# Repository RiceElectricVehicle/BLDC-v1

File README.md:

# BLDC-v1
REV BLDC Controller Version 1 2019-2020

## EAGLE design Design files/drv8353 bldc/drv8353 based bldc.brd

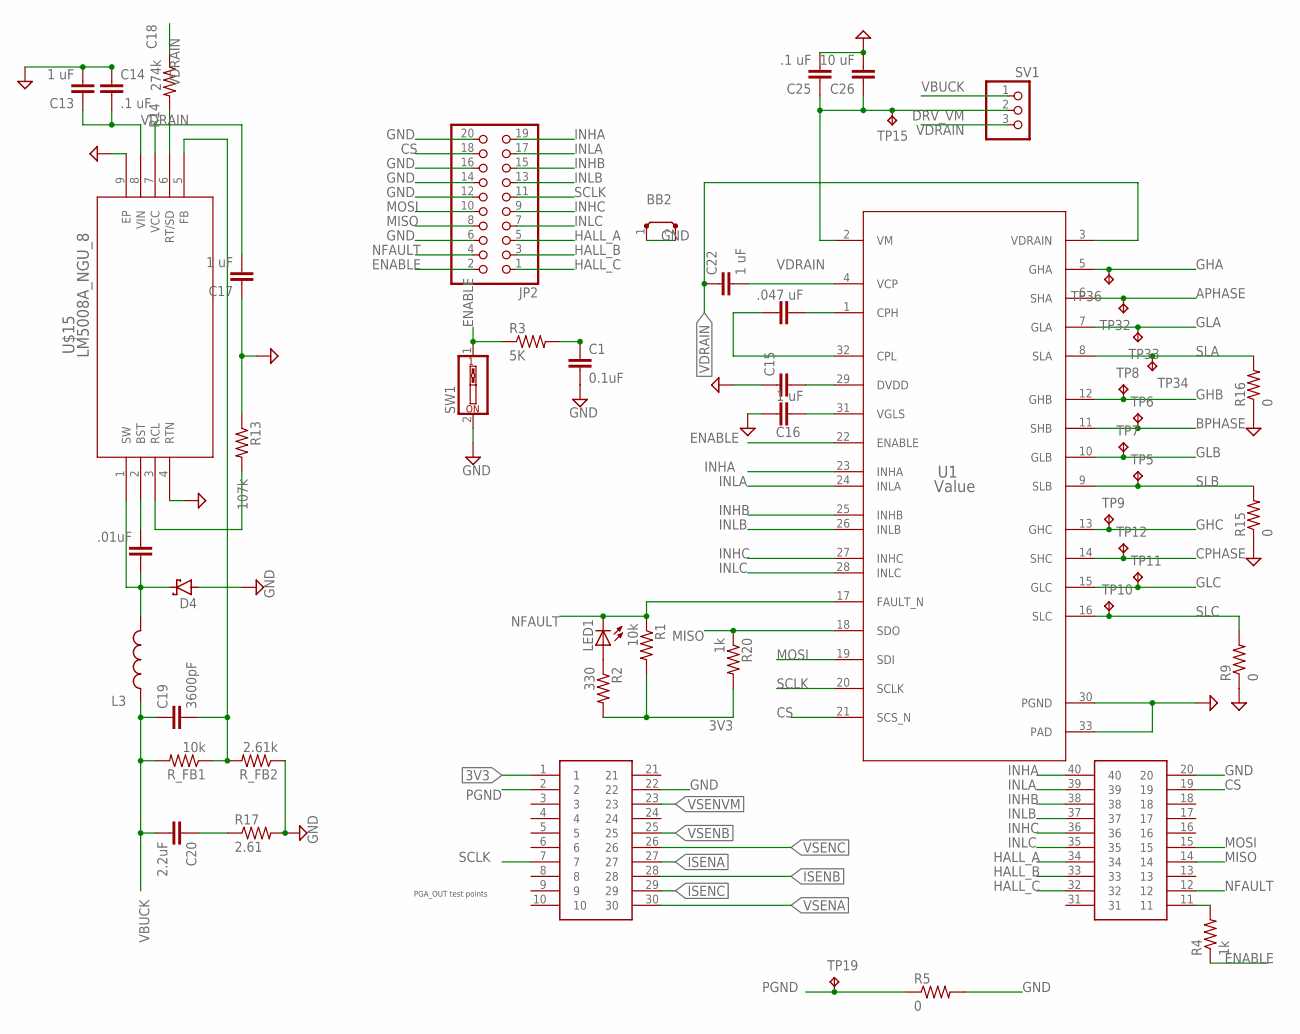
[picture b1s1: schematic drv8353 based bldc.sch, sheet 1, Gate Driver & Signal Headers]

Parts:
BB2: TE3/2
C1: 0.1uF; C0603K
C13: 1 uF; C1206K
C14, C25: .1 uF; C0805K
C15, C16, C17, C22: 1 uF; C0603K
C18: .01uF; C0603K
C19: 3600pF; C0603K
C20: 2.2uF; C0805K
C21: .047 uF; C0805K
C26: 10 uF; C2220K
D4: DFLS1200
JP2: PINHD-2X10; 2X10
L3: 330 uH; 74404084331
LED1: LED_ESML0603; LED_SML0603
R1: 10k; R0603
R2: 330; R0603
R3: 5K; R0603
R4, R20: 1k; R0603
R5, R9, R15, R16: 0; R0603
R13: 107k; R0603
R14: 274k; R0603
R17: 2.61; R0603
R_FB1: 10k; R0603
R_FB2: 2.61k; R0603
SV1: PINHD-1X3; 1X03
SW1: SW_DIP-1; EDG-01
TP5, TP6, TP7, TP8, TP9, TP10, TP11, TP12, TP15, TP19, TP32, TP33, TP34, TP36: TPB1,27; B1,27
U1: Value; RTV0032E
U$2: BOOSTER_DOCK
U$15: LM5008A_NGU_8; SDC08B

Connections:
3V3: R1.2, R2.2, R20.2, U$2.1; also elsewhere on the board
APHASE: TP32.TP, U1.6 (SHA); also elsewhere on the board
BPHASE: TP6.TP, U1.11 (SHB); also elsewhere on the board
BST: C18.2, U$15.2 (BST)
CPHASE: TP12.TP, U1.14 (SHC); also elsewhere on the board
CS: JP2.18, U1.21 (SCS_N), U$2.19
DRV_VM: C25.1, C26.1, SV1.2, TP15.TP, U1.2 (VM)
ENABLE: JP2.2, R3.1, R4.1, SW1.1, U1.22 (ENABLE)
FB: C19.2, R_FB1.1, R_FB2.2, U$15.5 (FB)
GHA: TP36.TP, U1.5 (GHA); also elsewhere on the board
GHB: TP8.TP, U1.12 (GHB); also elsewhere on the board
GHC: TP9.TP, U1.13 (GHC); also elsewhere on the board
GLA: TP33.TP, U1.7 (GLA); also elsewhere on the board
GLB: TP7.TP, U1.10 (GLB); also elsewhere on the board
GLC: TP11.TP, U1.15 (GLC); also elsewhere on the board
GND: BB2.1, BB2.2, C1.2, C13.2, C14.1, C15.1, C16.1, C17.1, C25.2, C26.2, D4.GND, JP2.6, JP2.12, JP2.14, JP2.16, JP2.20, R5.2, R9.1, R13.1, R15.1, R16.1, R17.2, R_FB2.1, SW1.2, U1.30 (PGND), U1.33 (PAD), U$2.20, U$2.22, U$15.4 (RTN), U$15.9 (EP); also elsewhere on the board
HALL_A: JP2.5, U$2.34; also elsewhere on the board
HALL_B: JP2.3, U$2.33; also elsewhere on the board
HALL_C: JP2.1, U$2.32; also elsewhere on the board
INHA: JP2.19, U1.23 (INHA), U$2.40
INHB: JP2.15, U1.25 (INHB), U$2.38
INHC: JP2.9, U1.27 (INHC), U$2.36
INLA: JP2.17, U1.24 (INLA), U$2.39
INLB: JP2.13, U1.26 (INLB), U$2.37
INLC: JP2.7, U1.28 (INLC), U$2.35
ISENA: U$2.27; also elsewhere on the board
ISENB: U$2.28; also elsewhere on the board
ISENC: U$2.29; also elsewhere on the board
MISO: JP2.8, R20.1, U1.18 (SDO), U$2.14
MOSI: JP2.10, U1.19 (SDI), U$2.15
unnamed: C15.2, U1.29 (DVDD)
unnamed: C22.2, U1.4 (VCP)
unnamed: C21.2, U1.1 (CPH)
unnamed: C21.1, U1.32 (CPL)
unnamed: C16.2, U1.31 (VGLS)
unnamed: R4.2, U$2.11
unnamed: C20.1, R17.1
unnamed: LED1.A, R2.1
unnamed: C1.1, R3.2
NFAULT: JP2.4, LED1.C, R1.1, U1.17 (FAULT_N), U$2.12
PGND: R5.1, TP19.TP, U$2.2
RCL: R13.2, U$15.3 (RCL)
RT/SD: R14.2, U$15.6 (RT/SD)
SCLK: JP2.11, U1.20 (SCLK), U$2.7
SLA: R16.2, TP34.TP, U1.8 (SLA)
SLB: R15.2, TP5.TP, U1.9 (SLB)
SLC: R9.2, TP10.TP, U1.16 (SLC)
SW: C18.1, D4.LINE, L3.P$2 (2), U$15.1 (SW)
VBUCK: C19.1, C20.2, L3.P$1 (1), R_FB1.2, SV1.1; also elsewhere on the board
VCC: C17.2, U$15.7 (VCC)
VDRAIN: C13.1, C14.2, C22.1, R14.1, SV1.3, U1.3 (VDRAIN), U$15.8 (VIN); also elsewhere on the board
VSENA: U$2.30; also elsewhere on the board
VSENB: U$2.25; also elsewhere on the board
VSENC: U$2.26; also elsewhere on the board
VSENVM: U$2.23; also elsewhere on the board

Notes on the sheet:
PGA_OUT test points

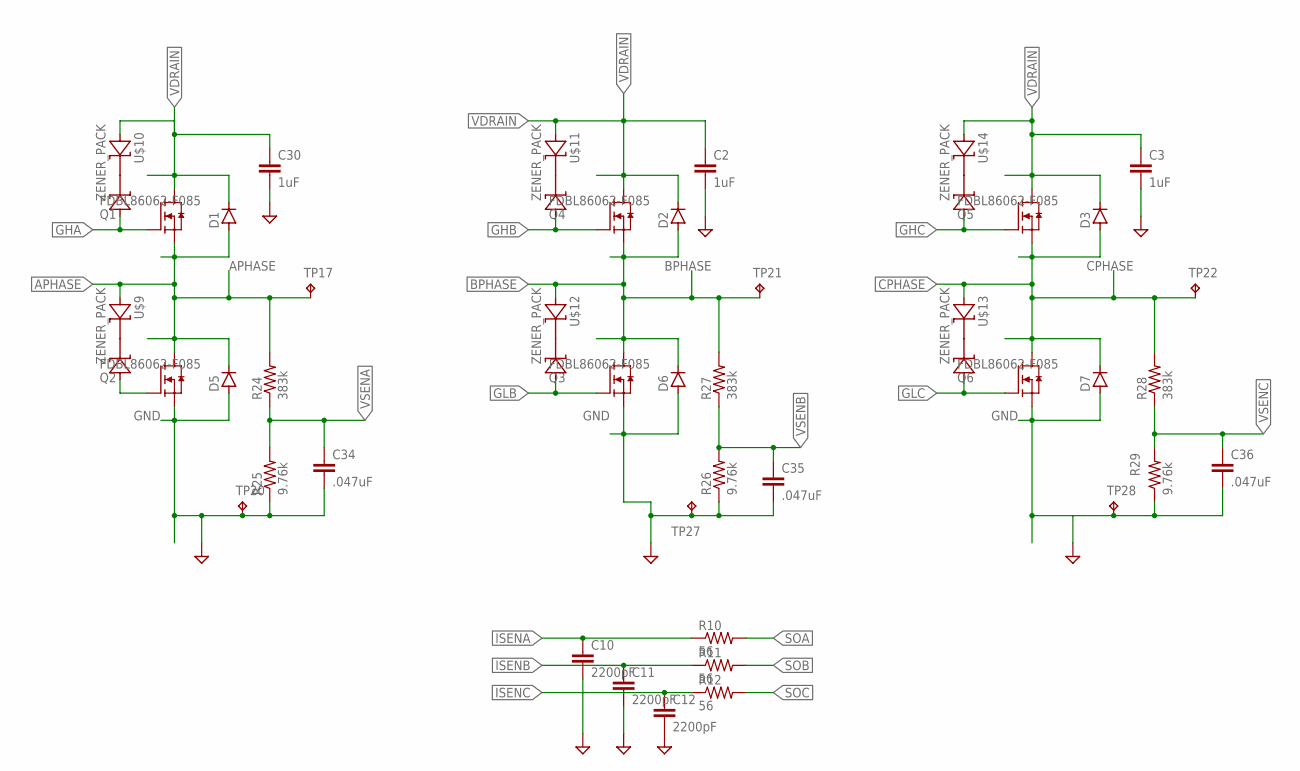
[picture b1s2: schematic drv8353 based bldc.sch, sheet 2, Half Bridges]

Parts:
C2, C3, C30: 1uF; C1206
C10, C11, C12: 2200pF; C0603K
C34, C35, C36: .047uF; C0603K
D1, D2, D3, D5, D6, D7: D-SOD123; SOD123
Q1, Q2, Q3, Q4, Q5, Q6: FDBL86062-F085; H-PSOF8L-11.68X9.80_1
R10, R11, R12: 56; R0603
R24, R27, R28: 383k; R0603
R25, R26, R29: 9.76k; R0603
TP17, TP20, TP21, TP22, TP27, TP28: TPB1,27; B1,27
U$9, U$10, U$11, U$12, U$13, U$14: ZENER_PACK; SOT23-CLIPPED-LEG

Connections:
APHASE: D1.2 (A), D5.LINE (C), Q1.S2 (S), Q1.S3 (S), Q1.S4 (S), Q1.S5 (S), Q1.S6 (S), Q1.S7 (S), Q1.S8 (S), Q2.D, Q2.D10 (D), Q2.D11 (D), Q2.D12 (D), Q2.D13 (D), R24.2, TP17.TP, U$9.2 (END2); also elsewhere on the board
BPHASE: D2.2 (A), D6.LINE (C), Q3.D, Q3.D10 (D), Q3.D11 (D), Q3.D12 (D), Q3.D13 (D), Q4.S2 (S), Q4.S3 (S), Q4.S4 (S), Q4.S5 (S), Q4.S6 (S), Q4.S7 (S), Q4.S8 (S), R27.2, TP21.TP, U$12.2 (END2); also elsewhere on the board
CPHASE: D3.2 (A), D7.LINE (C), Q5.S2 (S), Q5.S3 (S), Q5.S4 (S), Q5.S5 (S), Q5.S6 (S), Q5.S7 (S), Q5.S8 (S), Q6.D, Q6.D10 (D), Q6.D11 (D), Q6.D12 (D), Q6.D13 (D), R28.2, TP22.TP, U$13.2 (END2); also elsewhere on the board
GHA: Q1.G, U$10.1 (END1); also elsewhere on the board
GHB: Q4.G, U$11.1 (END1); also elsewhere on the board
GHC: Q5.G, U$14.1 (END1); also elsewhere on the board
GLA: Q2.G, U$9.1 (END1); also elsewhere on the board
GLB: Q3.G, U$12.1 (END1); also elsewhere on the board
GLC: Q6.G, U$13.1 (END1); also elsewhere on the board
GND: C2.2, C3.2, C10.2, C11.2, C12.2, C30.2, C34.2, C35.2, C36.2, D5.2 (A), D6.2 (A), D7.2 (A), Q2.S2 (S), Q2.S3 (S), Q2.S4 (S), Q2.S5 (S), Q2.S6 (S), Q2.S7 (S), Q2.S8 (S), Q3.S2 (S), Q3.S3 (S), Q3.S4 (S), Q3.S5 (S), Q3.S6 (S), Q3.S7 (S), Q3.S8 (S), Q6.S2 (S), Q6.S3 (S), Q6.S4 (S), Q6.S5 (S), Q6.S6 (S), Q6.S7 (S), Q6.S8 (S), R25.1, R26.1, R29.1, TP20.TP, TP27.TP, TP28.TP; also elsewhere on the board
ISENA: C10.1, R10.1; also elsewhere on the board
ISENB: C11.1, R11.1; also elsewhere on the board
ISENC: C12.1, R12.1; also elsewhere on the board
SOA: R10.2
SOB: R11.2
SOC: R12.2
VDRAIN: C2.1, C3.1, C30.1, D1.LINE (C), D2.LINE (C), D3.LINE (C), Q1.D, Q1.D10 (D), Q1.D11 (D), Q1.D12 (D), Q1.D13 (D), Q4.D, Q4.D10 (D), Q4.D11 (D), Q4.D12 (D), Q4.D13 (D), Q5.D, Q5.D10 (D), Q5.D11 (D), Q5.D12 (D), Q5.D13 (D), U$10.2 (END2), U$11.2 (END2), U$14.2 (END2); also elsewhere on the board
VSENA: C34.1, R24.1, R25.2; also elsewhere on the board
VSENB: C35.1, R26.2, R27.1; also elsewhere on the board
VSENC: C36.1, R28.1, R29.2; also elsewhere on the board

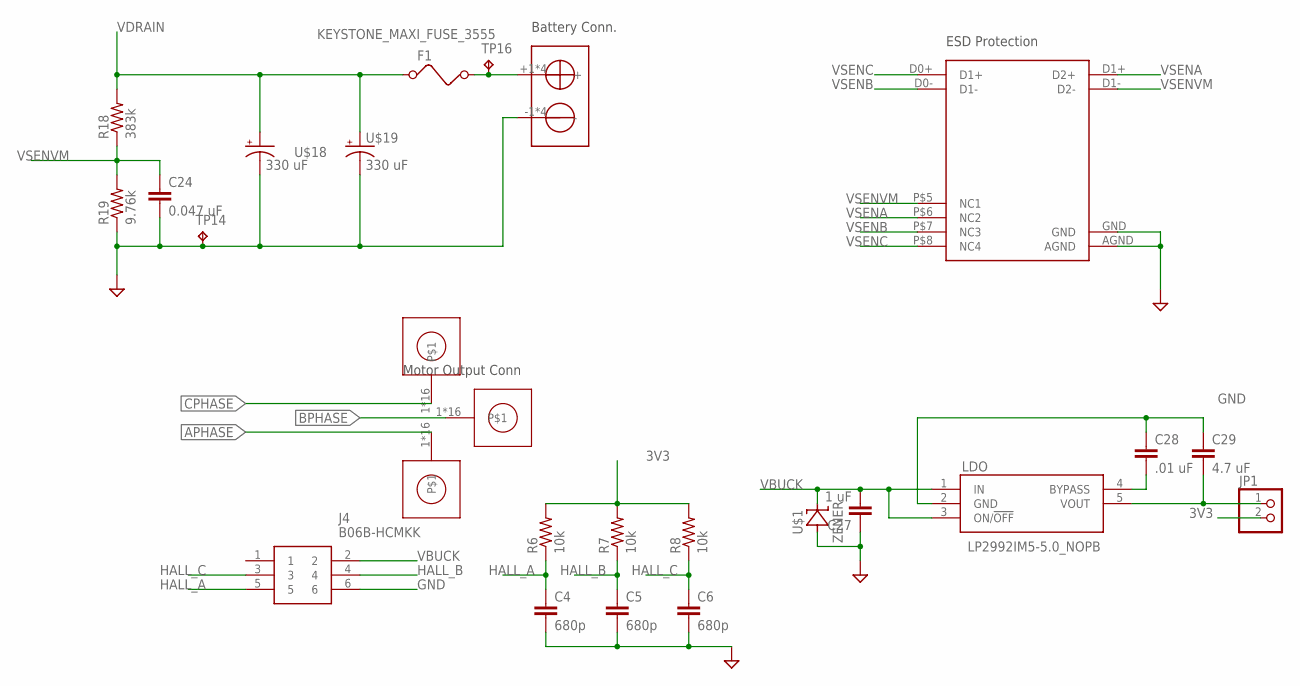
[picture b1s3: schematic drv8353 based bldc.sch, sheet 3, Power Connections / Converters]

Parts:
C4, C5, C6: 680p; C0603K
C24: 0.047 uF; C0603K
C27: 1 uF; C0805K
C28: .01 uF; C0603K
C29: 4.7 uF; C1210K
F1: KEYSTONE_MAXI_FUSE_3555; KEYSTONE_MAXI_FUSE_CLIP_3555
J1, J2, J3: 7461147; 7461147_REDCUBE
J4: B06B-HCMKK; B06BHCMKK
JP1: PINHD-1X2; 1X02
LDO: LP2992IM5-5.0_NOPB; SOT95P280X145-5N
R6, R7, R8: 10k; R0603
R18: 383k; R0603
R19: 9.76k; R0603
TP14, TP16: TPB1,27; B1,27
TVS_DIODE: TPD4S010DQAR
U$1: ZENER; SOD123
U$16: SB50; MINI-SB-50
U$18, U$19: 330 uF; SM_RADIAL_K16_1PRIMARY

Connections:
3V3: JP1.2, R6.2, R7.2, R8.2; also elsewhere on the board
APHASE: J2.1, J2.2, J2.3, J2.4, J2.5, J2.6, J2.7, J2.8, J2.9, J2.10, J2.11, J2.12, J2.13, J2.14, J2.15, J2.16; also elsewhere on the board
BPHASE: J3.1, J3.2, J3.3, J3.4, J3.5, J3.6, J3.7, J3.8, J3.9, J3.10, J3.11, J3.12, J3.13, J3.14, J3.15, J3.16; also elsewhere on the board
CPHASE: J1.1, J1.2, J1.3, J1.4, J1.5, J1.6, J1.7, J1.8, J1.9, J1.10, J1.11, J1.12, J1.13, J1.14, J1.15, J1.16; also elsewhere on the board
GND: C4.2, C5.2, C6.2, C24.2, C27.1, C28.1, C29.1, J4.6, LDO.2 (GND), R19.1, TP14.TP, TVS_DIODE.AGND, TVS_DIODE.GND, U$1.2 (A), U$16.-1 (-), U$16.-2 (-), U$16.-3 (-), U$16.-4 (-), U$18.-, U$19.-; also elsewhere on the board
HALL_A: C4.1, J4.5, R6.1; also elsewhere on the board
HALL_B: C5.1, J4.4, R7.1; also elsewhere on the board
HALL_C: C6.1, J4.3, R8.1; also elsewhere on the board
unnamed: C29.2, JP1.1, LDO.5 (VOUT)
unnamed: C28.2, LDO.4 (BYPASS)
unnamed: F1.B1 (2), F1.B2 (2), TP16.TP, U$16.+1 (+), U$16.+2 (+), U$16.+3 (+), U$16.+4 (+)
VBUCK: C27.2, J4.2, LDO.1 (IN), LDO.3 (ON/!OFF), U$1.LINE; also elsewhere on the board
VDRAIN: F1.A1 (1), F1.A2 (1), R18.2, U$18.+, U$19.+; also elsewhere on the board
VSENA: TVS_DIODE.D1+ (D2+), TVS_DIODE.P$6 (NC2); also elsewhere on the board
VSENB: TVS_DIODE.D0- (D1-), TVS_DIODE.P$7 (NC3); also elsewhere on the board
VSENC: TVS_DIODE.D0+ (D1+), TVS_DIODE.P$8 (NC4); also elsewhere on the board
VSENVM: C24.1, R18.1, R19.2, TVS_DIODE.D1- (D2-), TVS_DIODE.P$5 (NC1); also elsewhere on the board

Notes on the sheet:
ESD Protection
Battery Conn.
Motor Output Conn

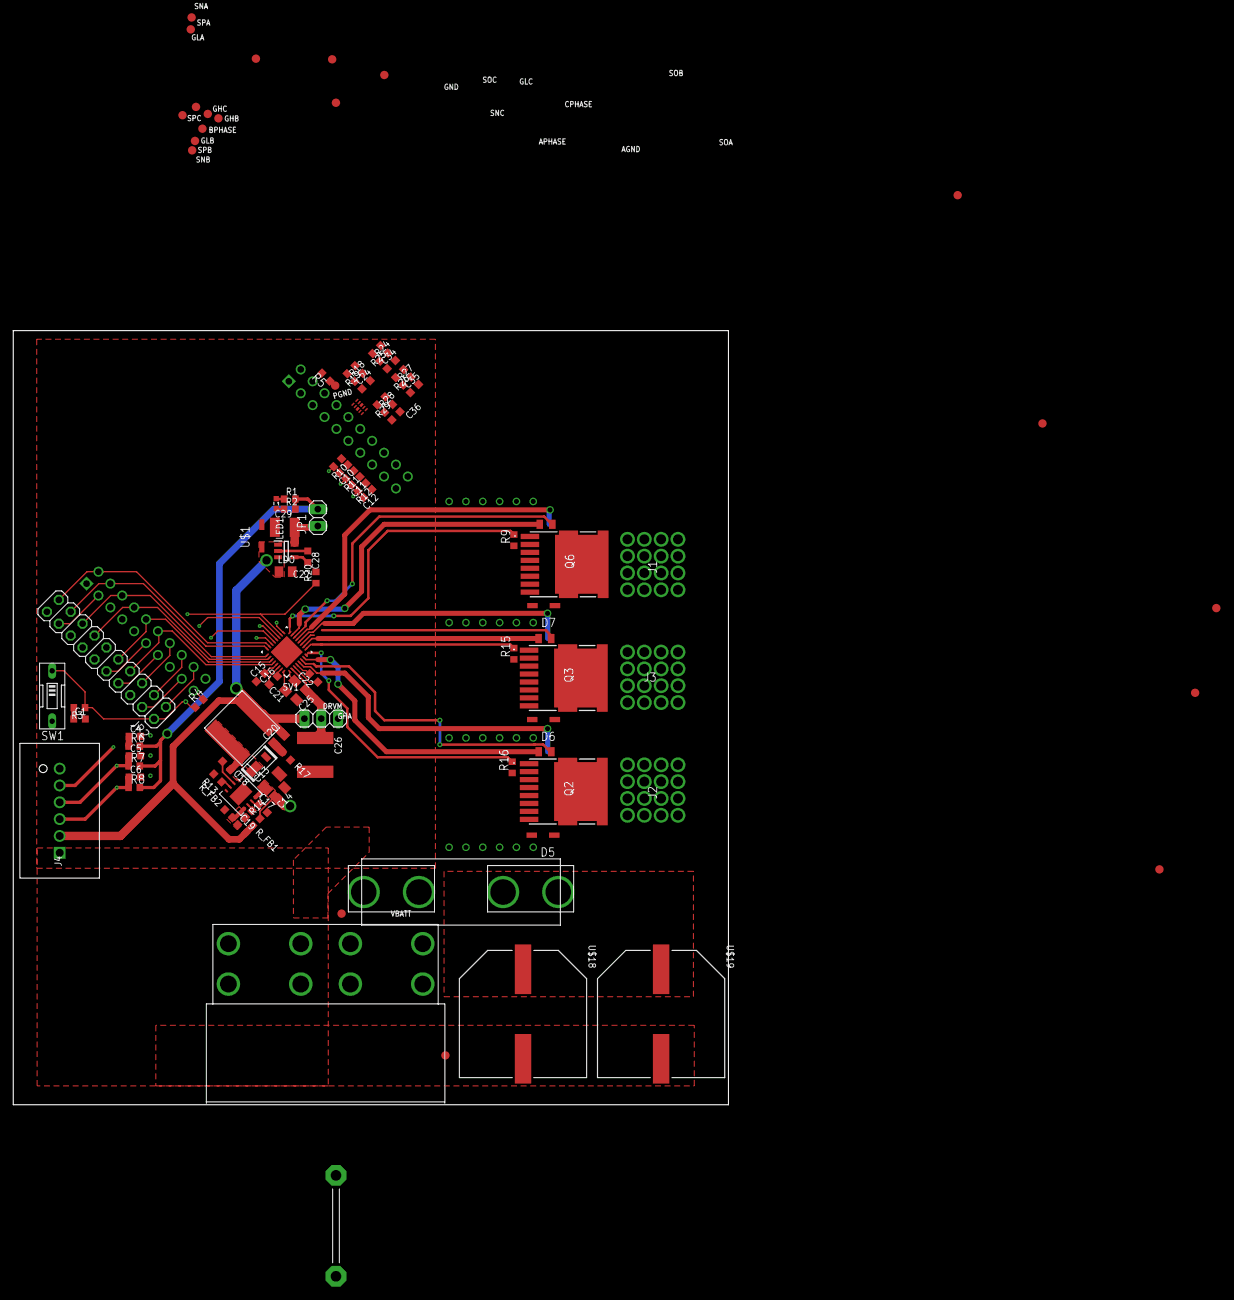
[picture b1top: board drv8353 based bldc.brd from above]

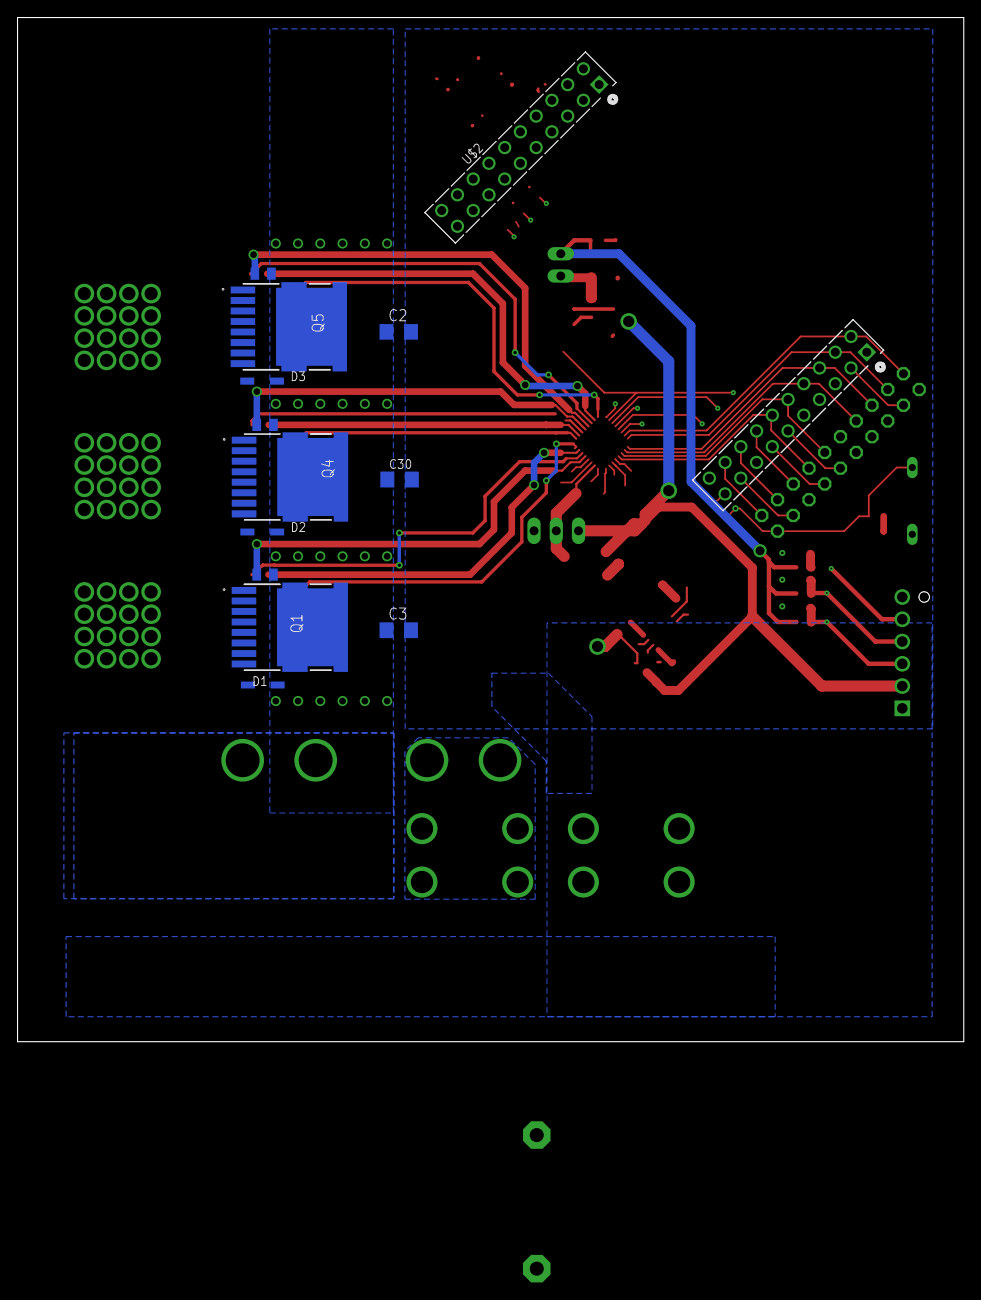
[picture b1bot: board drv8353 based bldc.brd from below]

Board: 4 copper layers, 108.0 x 116.8 mm, 119 parts (13 on the bottom side), 58 nets.

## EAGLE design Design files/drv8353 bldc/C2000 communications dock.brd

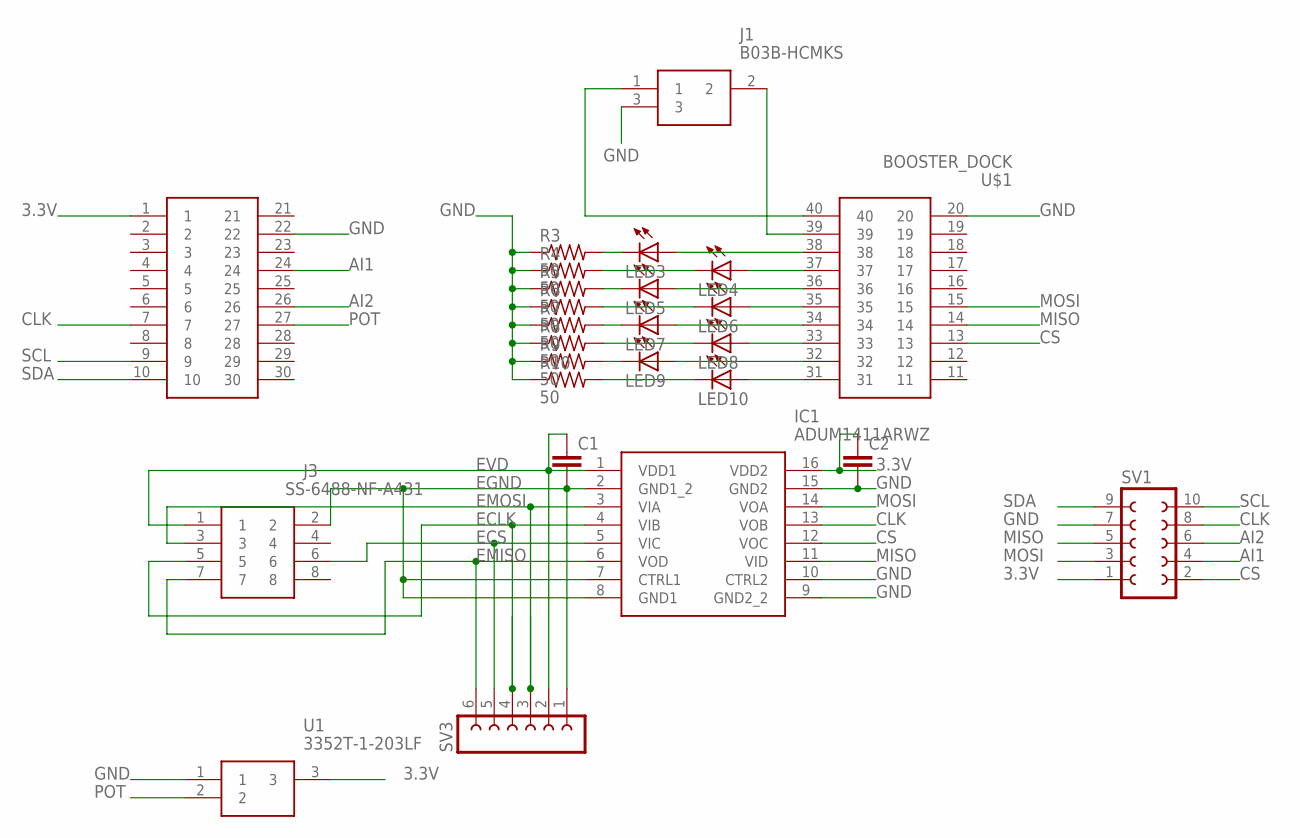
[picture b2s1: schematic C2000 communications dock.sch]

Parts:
C1, C2: C-EUC0603; C0603
IC1: ADUM1411ARWZ; SOIC127P1032X265-16N
J1: B03B-HCMKS; B03BHCMKS
J3: SS-6488-NF-A431; SS6488NFA431
LED3, LED4, LED5, LED6, LED7, LED8, LED9, LED10: LED_ESML0603; LED_SML0603
R3, R4, R5, R6, R7, R8, R9, R10: 50; R0603
SV1: FE05-2
SV3: FE06-1; FE06
U1: 3352T-1-203LF
U$1: BOOSTER_DOCK

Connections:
3.3V: C2.1, IC1.16 (VDD2), SV1.1, U1.3, U$1.1
AI1: SV1.4, U$1.24
AI2: SV1.6, U$1.26
CLK: IC1.13 (VOB), SV1.8, U$1.7
CS: IC1.12 (VOC), SV1.2, U$1.13
ECLK: IC1.4 (VIB), J3.5, SV3.4
ECS: IC1.5 (VIC), J3.6, SV3.5
EGND: C1.2, IC1.2 (GND1_2), IC1.7 (CTRL1), IC1.8 (GND1), J3.2, SV3.1
EMISO: IC1.6 (VOD), J3.7, SV3.6
EMOSI: IC1.3 (VIA), J3.3, SV3.3
EVD: C1.1, IC1.1 (VDD1), J3.1, SV3.2
GND: C2.2, IC1.9 (GND2_2), IC1.10 (CTRL2), IC1.15 (GND2), J1.3, R3.1, R4.1, R5.1, R6.1, R7.1, R8.1, R9.1, R10.1, SV1.7, U1.1, U$1.20, U$1.22
MISO: IC1.11 (VID), SV1.5, U$1.14
MOSI: IC1.14 (VOA), SV1.3, U$1.15
unnamed: J1.1, U$1.40
unnamed: J1.2, U$1.39
unnamed: LED3.A, U$1.38
unnamed: LED4.A, U$1.37
unnamed: LED5.A, U$1.36
unnamed: LED6.A, U$1.35
unnamed: LED7.A, U$1.34
unnamed: LED8.A, U$1.33
unnamed: LED9.A, U$1.32
unnamed: LED10.A, U$1.31
unnamed: LED3.C, R3.2
unnamed: LED4.C, R4.2
unnamed: LED5.C, R5.2
unnamed: LED6.C, R6.2
unnamed: LED7.C, R7.2
unnamed: LED8.C, R8.2
unnamed: LED9.C, R9.2
unnamed: LED10.C, R10.2
POT: U1.2, U$1.27
SCL: SV1.10, U$1.9
SDA: SV1.9, U$1.10

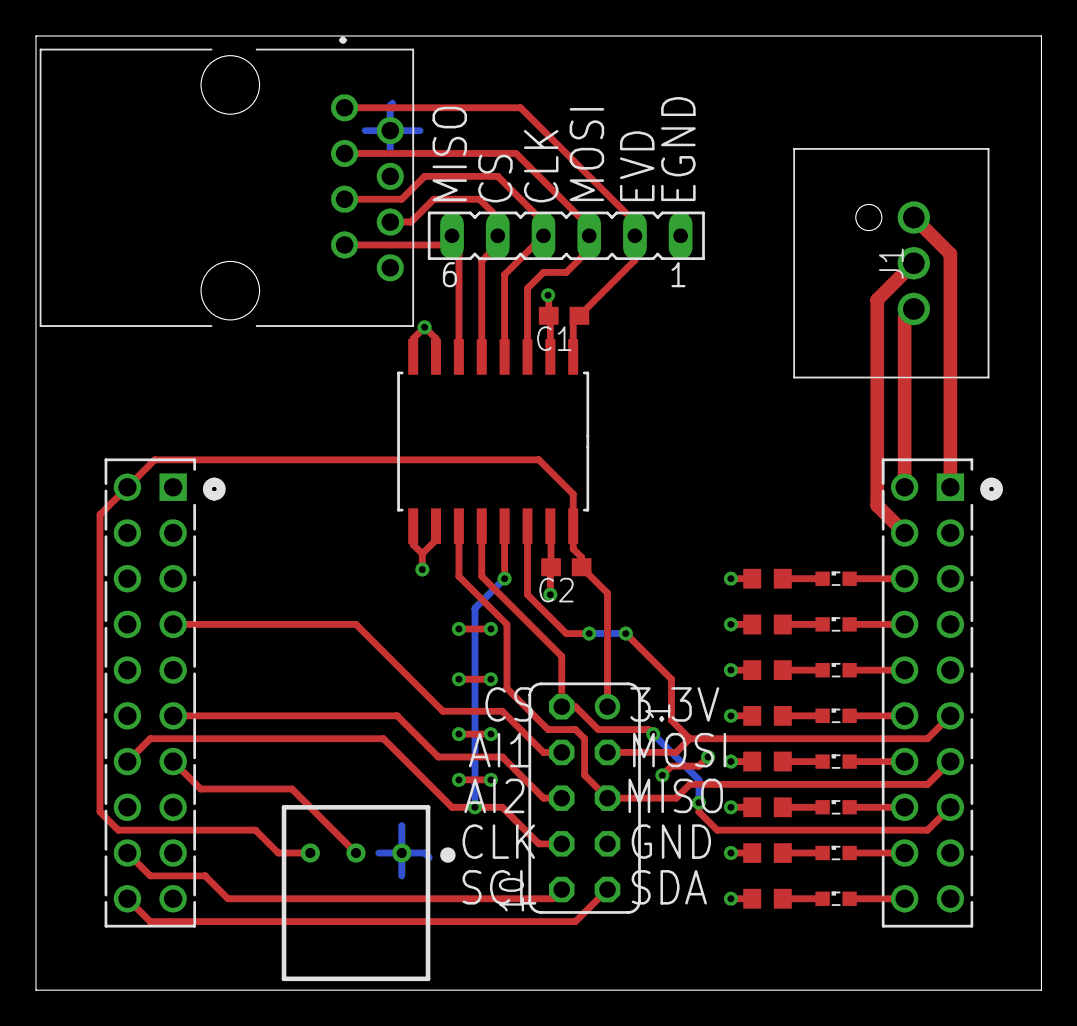
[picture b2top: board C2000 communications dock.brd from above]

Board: 2 copper layers, 55.9 x 53.0 mm, 25 parts (0 on the bottom side), 35 nets.

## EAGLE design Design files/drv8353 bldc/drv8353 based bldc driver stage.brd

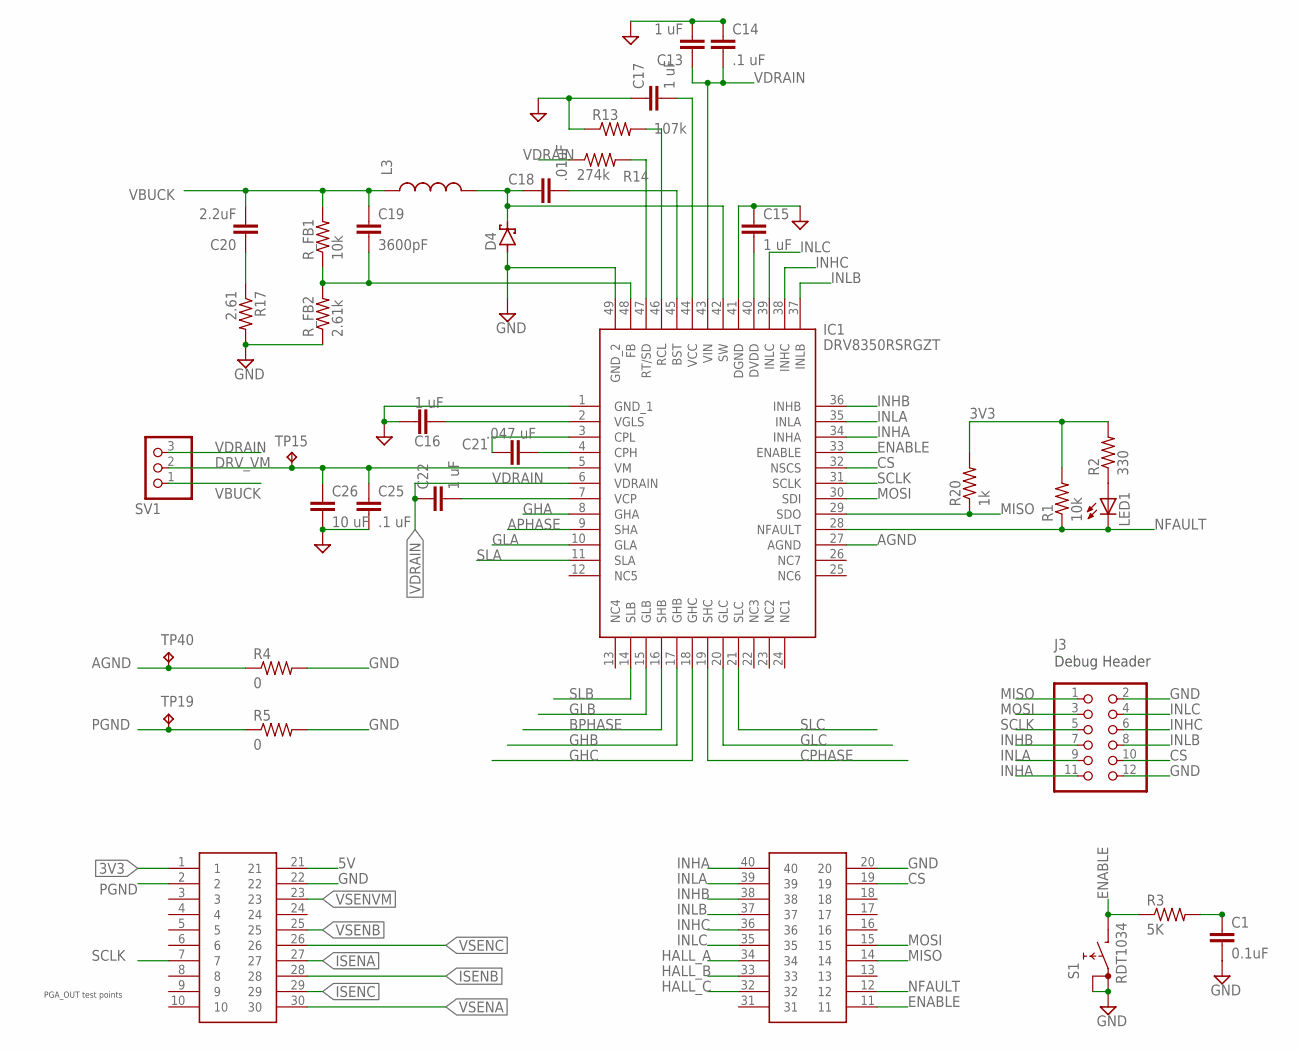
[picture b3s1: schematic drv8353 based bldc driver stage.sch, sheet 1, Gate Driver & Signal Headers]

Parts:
C1: 0.1uF; C0603K
C13: 1 uF; C1206K
C14, C25: .1 uF; C0805K
C15, C16, C17, C22: 1 uF; C0603K
C18: .01uF; C0603K
C19: 3600pF; C0603K
C20: 2.2uF; C0805K
C21: .047 uF; C0805K
C26: 10 uF; C2220K
D4: DFLS1200
IC1: DRV8350RSRGZT; QFN50P700X700X100-49N
J3: 2X6 FEMALE; 2X06
L3: 330 uH; 74404084331
LED1: LED_ESML0603; LED_SML0603
R1: 10k; R0603
R2: 330; R0603
R3: 5K; R0603
R4, R5: 0; R0603
R13: 107k; R0603
R14: 274k; R0603
R17: 2.61; R0603
R20: 1k; R0603
R_FB1: 10k; R0603
R_FB2: 2.61k; R0603
S1: RDT1034
SV1: PINHD-1X3; 1X03
TP15, TP19, TP40: TPB1,27; B1,27
U$2: BOOSTER_DOCK

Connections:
3V3: R1.2, R2.2, R20.2, U$2.1; also elsewhere on the board
5V: U$2.21; also elsewhere on the board
AGND: IC1.27 (AGND), R4.1, TP40.TP
APHASE: IC1.9 (SHA); also elsewhere on the board
BPHASE: IC1.16 (SHB); also elsewhere on the board
BST: C18.2, IC1.45 (BST)
CPH: C21.2, IC1.4 (CPH)
CPHASE: IC1.19 (SHC); also elsewhere on the board
CPL: C21.1, IC1.3 (CPL)
CS: IC1.32 (NSCS), J3.10, U$2.19
DRV_VM: C25.1, C26.1, IC1.5 (VM), SV1.2, TP15.TP
ENABLE: IC1.33 (ENABLE), R3.1, S1.B, U$2.11
FB: C19.2, IC1.48 (FB), R_FB1.1, R_FB2.2
GHA: IC1.8 (GHA); also elsewhere on the board
GHB: IC1.17 (GHB); also elsewhere on the board
GHC: IC1.18 (GHC); also elsewhere on the board
GLA: IC1.10 (GLA); also elsewhere on the board
GLB: IC1.15 (GLB); also elsewhere on the board
GLC: IC1.20 (GLC); also elsewhere on the board
GND: C1.2, C13.2, C14.1, C15.1, C16.1, C17.1, C25.2, C26.2, D4.GND, IC1.1 (GND_1), IC1.41 (DGND), IC1.49 (GND_2), J3.2, J3.12, R4.2, R5.2, R13.1, R17.2, R_FB2.1, S1.A, S1.A1, U$2.20, U$2.22; also elsewhere on the board
HALL_A: U$2.34; also elsewhere on the board
HALL_B: U$2.33; also elsewhere on the board
HALL_C: U$2.32; also elsewhere on the board
INHA: IC1.34 (INHA), J3.11, U$2.40
INHB: IC1.36 (INHB), J3.7, U$2.38
INHC: IC1.38 (INHC), J3.6, U$2.36
INLA: IC1.35 (INLA), J3.9, U$2.39
INLB: IC1.37 (INLB), J3.8, U$2.37
INLC: IC1.39 (INLC), J3.4, U$2.35
ISENA: U$2.27; also elsewhere on the board
ISENB: U$2.28; also elsewhere on the board
ISENC: U$2.29; also elsewhere on the board
MISO: IC1.29 (SDO), J3.1, R20.1, U$2.14
MOSI: IC1.30 (SDI), J3.3, U$2.15
unnamed: C15.2, IC1.40 (DVDD)
unnamed: C20.1, R17.1
unnamed: LED1.A, R2.1
unnamed: C1.1, R3.2
NFAULT: IC1.28 (NFAULT), LED1.C, R1.1, U$2.12
PGND: R5.1, TP19.TP, U$2.2
RCL: IC1.46 (RCL), R13.2
RT/SD: IC1.47 (RT/SD), R14.2
SCLK: IC1.31 (SCLK), J3.5, U$2.7
SLA: IC1.11 (SLA); also elsewhere on the board
SLB: IC1.14 (SLB); also elsewhere on the board
SLC: IC1.21 (SLC); also elsewhere on the board
SW: C18.1, D4.LINE, IC1.42 (SW), L3.P$2 (2)
VBUCK: C19.1, C20.2, L3.P$1 (1), R_FB1.2, SV1.1; also elsewhere on the board
VCC: C17.2, IC1.44 (VCC)
VCP: C22.2, IC1.7 (VCP)
VDRAIN: C13.1, C14.2, C22.1, IC1.6 (VDRAIN), IC1.43 (VIN), R14.1, SV1.3; also elsewhere on the board
VGLS: C16.2, IC1.2 (VGLS)
VSENA: U$2.30; also elsewhere on the board
VSENB: U$2.25; also elsewhere on the board
VSENC: U$2.26; also elsewhere on the board
VSENVM: U$2.23; also elsewhere on the board

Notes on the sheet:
PGA_OUT test points
Debug Header

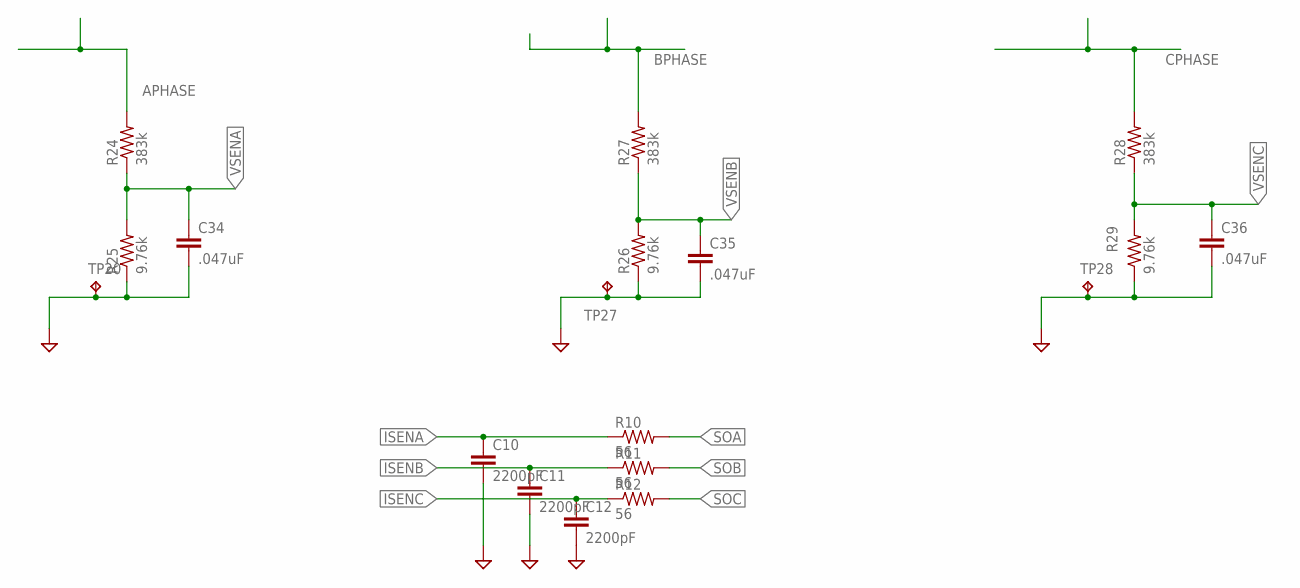
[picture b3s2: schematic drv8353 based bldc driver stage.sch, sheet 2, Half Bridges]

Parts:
C10, C11, C12: 2200pF; C0603K
C34, C35, C36: .047uF; C0603K
R10, R11, R12: 56; R0603
R24, R27, R28: 383k; R0603
R25, R26, R29: 9.76k; R0603
TP20, TP27, TP28: TPB1,27; B1,27

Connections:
APHASE: R24.2; also elsewhere on the board
BPHASE: R27.2; also elsewhere on the board
CPHASE: R28.2; also elsewhere on the board
GND: C10.2, C11.2, C12.2, C34.2, C35.2, C36.2, R25.1, R26.1, R29.1, TP20.TP, TP27.TP, TP28.TP; also elsewhere on the board
ISENA: C10.1, R10.1; also elsewhere on the board
ISENB: C11.1, R11.1; also elsewhere on the board
ISENC: C12.1, R12.1; also elsewhere on the board
SOA: R10.2; also elsewhere on the board
SOB: R11.2; also elsewhere on the board
SOC: R12.2; also elsewhere on the board
VSENA: C34.1, R24.1, R25.2; also elsewhere on the board
VSENB: C35.1, R26.2, R27.1; also elsewhere on the board
VSENC: C36.1, R28.1, R29.2; also elsewhere on the board

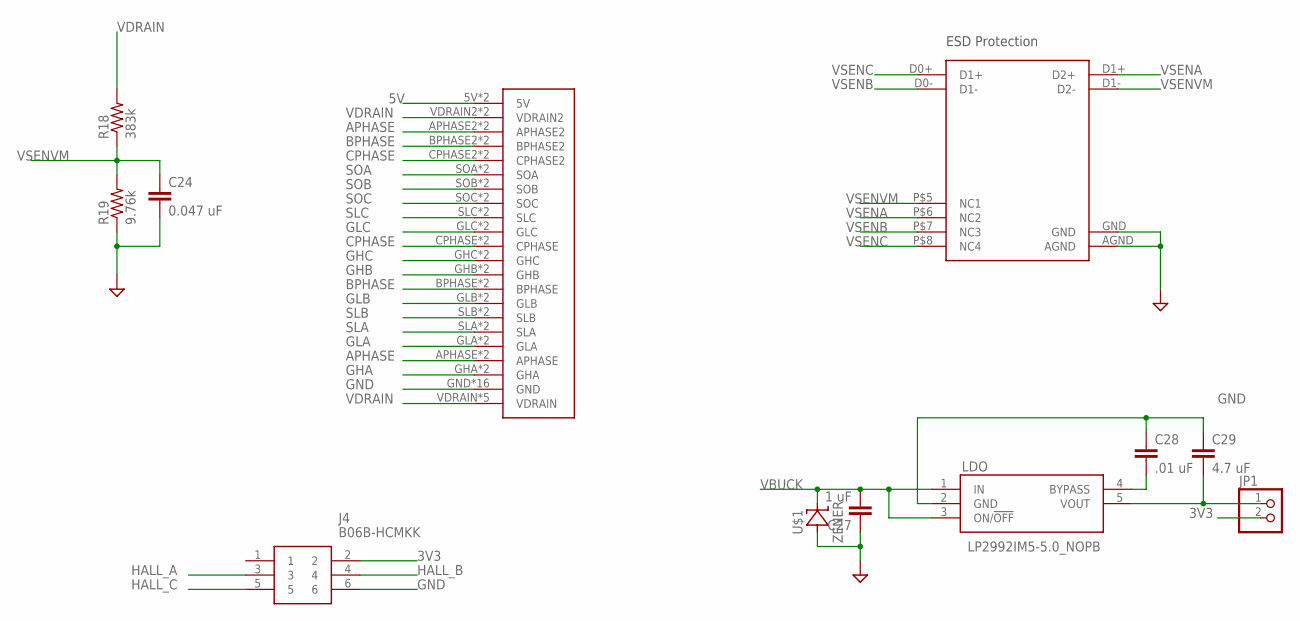
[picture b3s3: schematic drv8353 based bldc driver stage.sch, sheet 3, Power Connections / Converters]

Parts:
C24: 0.047 uF; C0603K
C27: 1 uF; C0805K
C28: .01 uF; C0603K
C29: 4.7 uF; C1210K
J4: B06B-HCMKK; B06BHCMKK
JP1: PINHD-1X2; 1X02
LDO: LP2992IM5-5.0_NOPB; SOT95P280X145-5N
R18: 383k; R0603
R19: 9.76k; R0603
TVS_DIODE: TPD4S010DQAR
U$1: ZENER; SOD123
U$3: DRIVER_STAGE_CONNECTORDRIVER; DRIVER_STAGE_CONNECTION

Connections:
3V3: J4.2, JP1.2; also elsewhere on the board
5V: U$3.5V, U$3.5VH (5V); also elsewhere on the board
APHASE: U$3.APHASE, U$3.APHASE2, U$3.APHASE2H (APHASE2), U$3.APHASEH (APHASE); also elsewhere on the board
BPHASE: U$3.BPHASE, U$3.BPHASE2, U$3.BPHASE2H (BPHASE2), U$3.BPHASEH (BPHASE); also elsewhere on the board
CPHASE: U$3.CPHASE, U$3.CPHASE2, U$3.CPHASE2H (CPHASE2), U$3.CPHASEH (CPHASE); also elsewhere on the board
GHA: U$3.GHA, U$3.GHAH (GHA); also elsewhere on the board
GHB: U$3.GHB, U$3.GHBH (GHB); also elsewhere on the board
GHC: U$3.GHC, U$3.GHCH (GHC); also elsewhere on the board
GLA: U$3.GLA, U$3.GLAH (GLA); also elsewhere on the board
GLB: U$3.GLB, U$3.GLBH (GLB); also elsewhere on the board
GLC: U$3.GLC, U$3.GLCH (GLC); also elsewhere on the board
GND: C24.2, C27.1, C28.1, C29.1, J4.6, LDO.2 (GND), R19.1, TVS_DIODE.AGND, TVS_DIODE.GND, U$1.2 (A), U$3.GND, U$3.GND2 (GND), U$3.GND2H1 (GND), U$3.GND2H2 (GND), U$3.GND2H3 (GND), U$3.GND2H4 (GND), U$3.GND2H5 (GND), U$3.GND2H6 (GND), U$3.GND2H7 (GND), U$3.GND2H8 (GND), U$3.GND2H9 (GND), U$3.GND2H10 (GND), U$3.GNDH1 (GND), U$3.GNDH2 (GND), U$3.GNDH3 (GND), U$3.GNDH4 (GND); also elsewhere on the board
HALL_A: J4.3; also elsewhere on the board
HALL_B: J4.4; also elsewhere on the board
HALL_C: J4.5; also elsewhere on the board
unnamed: C29.2, JP1.1, LDO.5 (VOUT)
unnamed: C28.2, LDO.4 (BYPASS)
SLA: U$3.SLA, U$3.SLAH (SLA); also elsewhere on the board
SLB: U$3.SLB, U$3.SLBH (SLB); also elsewhere on the board
SLC: U$3.SLC, U$3.SLCH (SLC); also elsewhere on the board
SOA: U$3.SOA, U$3.SOAH (SOA); also elsewhere on the board
SOB: U$3.SOB, U$3.SOBH (SOB); also elsewhere on the board
SOC: U$3.SOC, U$3.SOCH (SOC); also elsewhere on the board
VBUCK: C27.2, LDO.1 (IN), LDO.3 (ON/!OFF), U$1.LINE; also elsewhere on the board
VDRAIN: R18.2, U$3.VDRAIN, U$3.VDRAIN2, U$3.VDRAIN2H (VDRAIN2), U$3.VDRAINH1 (VDRAIN), U$3.VDRAINH2 (VDRAIN), U$3.VDRAINH3 (VDRAIN), U$3.VDRAINH4 (VDRAIN); also elsewhere on the board
VSENA: TVS_DIODE.D1+ (D2+), TVS_DIODE.P$6 (NC2); also elsewhere on the board
VSENB: TVS_DIODE.D0- (D1-), TVS_DIODE.P$7 (NC3); also elsewhere on the board
VSENC: TVS_DIODE.D0+ (D1+), TVS_DIODE.P$8 (NC4); also elsewhere on the board
VSENVM: C24.1, R18.1, R19.2, TVS_DIODE.D1- (D2-), TVS_DIODE.P$5 (NC1); also elsewhere on the board

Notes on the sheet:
ESD Protection

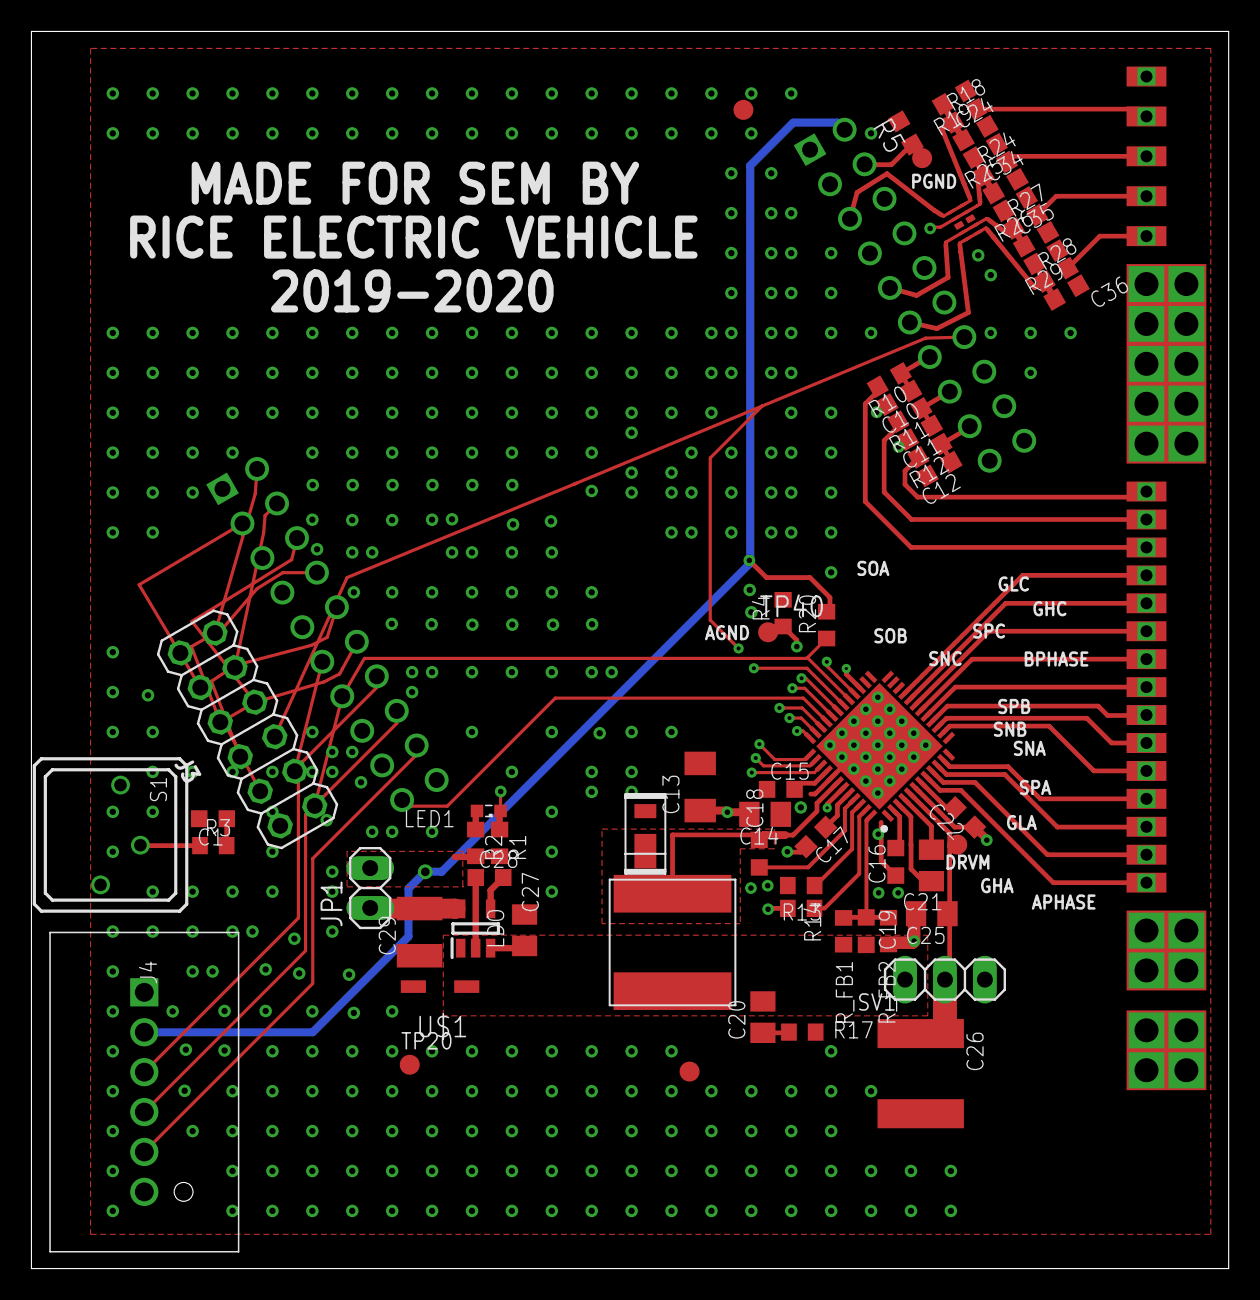
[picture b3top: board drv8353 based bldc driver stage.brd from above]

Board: 4 copper layers, 76.2 x 78.7 mm, 65 parts (1 on the bottom side), 61 nets.

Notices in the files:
Code/REV_CCS_workspace/REV_bldc/device/device.h:
$Copyright:
Copyright (C) 2019 Texas Instruments Incorporated - http://www.ti.com
